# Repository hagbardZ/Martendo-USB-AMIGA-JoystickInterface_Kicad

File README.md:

USB to DB9 Joystick Adapter

Connect your old Amiga/C64 Joystick to USB.

Pictures from the first working pizza oven soldered prototype:

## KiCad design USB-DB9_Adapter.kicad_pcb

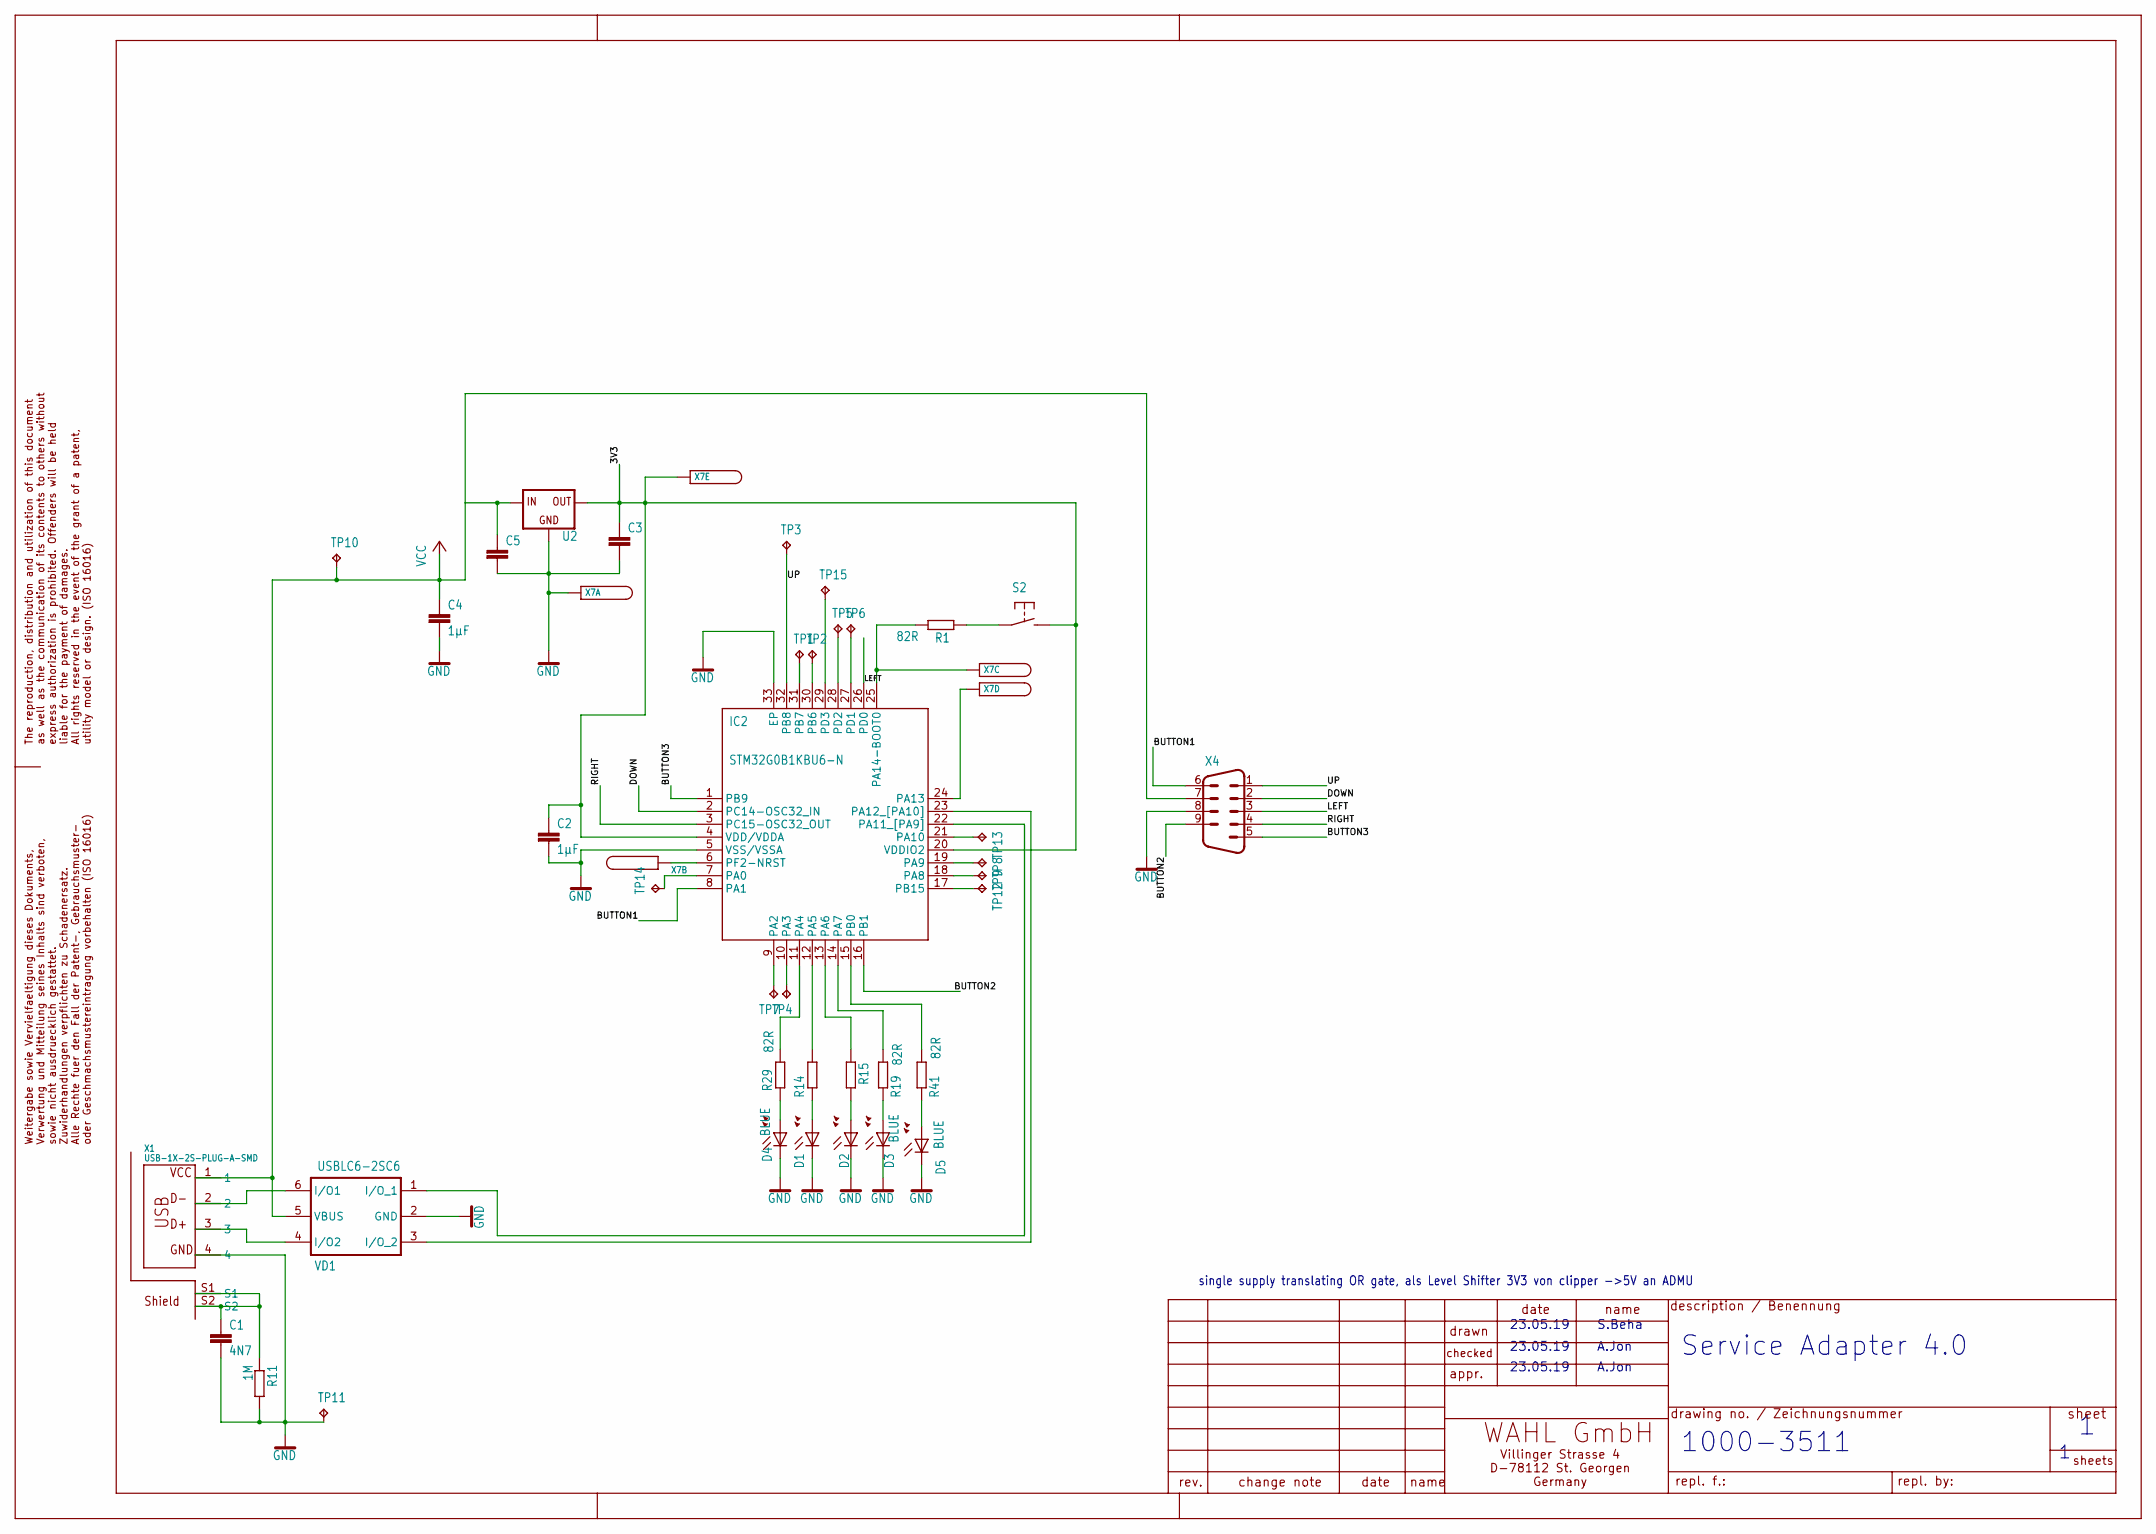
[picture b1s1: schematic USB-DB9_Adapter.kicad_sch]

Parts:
C1: 4N7; C0603
C2, C3, C4, C5: 1µF; C0603
D1: RED; 0805_D
D2: GREEN; 0805_D
D3, D4, D5: BLUE; 0805_D
IC2: STM32G0B1KBU6-N; QFN50P500X500X60-33N
R1, R14, R15, R19, R29, R41: 82R; 0603
R11: 1M; 0603
S2: TASER_KSR; KSR_TASTER
TP1, TP2, TP3, TP4, TP5, TP6, TP7, TP8, TP9, TP10, TP11, TP12, TP13, TP14, TP15: don't show; TESTPUNKT
U2: U_SPANNUNGSREGLERSOT23; SOT23
VD1: USBLC6-2SC6; SOT-23-6L
X1: USB-1X-2S-PLUG-A-SMD; USB-PLUG-A-SMD-2S
X4: M09H
X7: SWD_MOSER_CONN_5_POLST; SWD_MOSER_CONN_5_POL_.5MM

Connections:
/3V3: C2.1, C3.1, IC2.4 (VDD/VDDA), IC2.20 (VDDIO2), S2.P$2 (3), U2.E (OUT), X7.VDD (>NAME)
/BUTTON1: IC2.8 (PA1), X4.6
/BUTTON2: IC2.16 (PB1), X4.9
/BUTTON3: IC2.1 (PB9), X4.5
/DOWN: IC2.2 (PC14-OSC32_IN), X4.2
/LEFT: IC2.26 (PD0), X4.3
/RIGHT: IC2.3 (PC15-OSC32_OUT), X4.4
/UP: IC2.32 (PB8), TP3.TP (TP_TP), X4.1
GND: C1.2, C2.2, C3.2, C4.2, C5.2, D1.C, D2.C, D3.C, D4.C, D5.C, IC2.5 (VSS/VSSA), IC2.33 (EP), R11.2, TP11.TP (TP_TP), U2.B (GND), VD1.2 (GND), X1.4, X4.8, X7.GND (>NAME)
unnamed: C1.1, R11.1, X1.S1, X1.S2
unnamed: D1.A, R14.2
unnamed: D2.A, R15.2
unnamed: D3.A, R19.2
unnamed: D4.A, R29.2
unnamed: D5.A, R41.2
unnamed: IC2.7 (PA0), TP14.TP (TP_TP)
unnamed: IC2.9 (PA2), TP7.TP (TP_TP)
unnamed: IC2.10 (PA3), TP4.TP (TP_TP)
unnamed: IC2.11 (PA4), R29.1
unnamed: IC2.12 (PA5), R14.1
unnamed: IC2.13 (PA6), R15.1
unnamed: IC2.14 (PA7), R19.1
unnamed: IC2.18 (PA8), TP9.TP (TP_TP)
unnamed: IC2.19 (PA9), TP8.TP (TP_TP)
unnamed: IC2.21 (PA10), TP13.TP (TP_TP)
unnamed: IC2.22 (PA11_[PA9]), VD1.1 (I/O_1)
unnamed: IC2.23 (PA12_[PA10]), VD1.3 (I/O_2)
unnamed: IC2.24 (PA13), X7.SWDIO (>NAME)
unnamed: IC2.25 (PA14-BOOT0), R1.1, X7.SWDCLK (>NAME)
unnamed: IC2.15 (PB0), R41.1
unnamed: IC2.30 (PB6), TP2.TP (TP_TP)
unnamed: IC2.31 (PB7), TP1.TP (TP_TP)
unnamed: IC2.17 (PB15), TP12.TP (TP_TP)
unnamed: IC2.27 (PD1), TP6.TP (TP_TP)
unnamed: IC2.28 (PD2), TP5.TP (TP_TP)
unnamed: IC2.29 (PD3), TP15.TP (TP_TP)
unnamed: IC2.6 (PF2-NRST), X7.NRST (>NAME)
unnamed: R1.2, S2.P$1 (1)
unnamed: VD1.6 (I/O1), X1.2
unnamed: VD1.4 (I/O2), X1.3
VCC: C4.1, C5.1, TP10.TP (TP_TP), U2.C (IN), VD1.5 (VBUS), X1.1, X4.7

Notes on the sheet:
23.05.19
A.Jon
single supply translating OR gate, als Level Shifter 3V3 von clipper ->5V an ADMU
1000-3511
S.Beha
Service Adapter 4.0

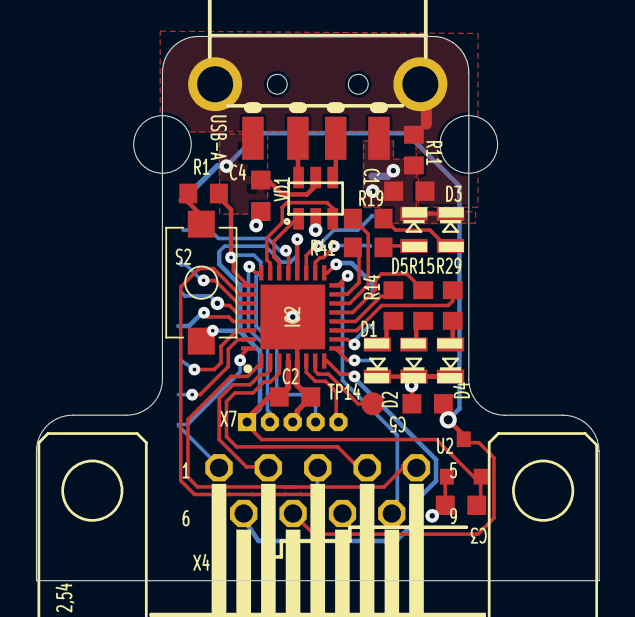
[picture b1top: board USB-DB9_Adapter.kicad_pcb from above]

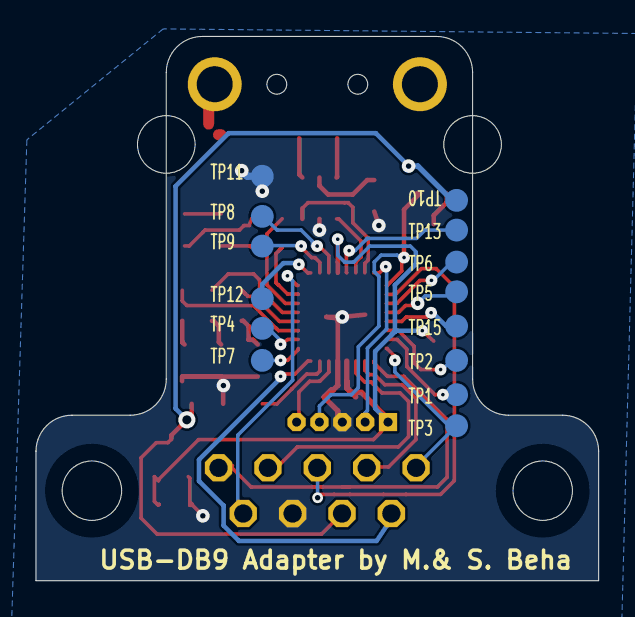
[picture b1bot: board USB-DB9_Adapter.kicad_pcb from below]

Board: 2 copper layers, 31.2 x 30.2 mm, 39 parts (14 on the bottom side), 41 nets.

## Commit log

2026-06-05 Update README.md
    added real pictures

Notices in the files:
USB-DB9_Adapter.kicad_sch:
All rights reserved in the event of the grant of a patent,
utility model or design. (ISO 16016)
